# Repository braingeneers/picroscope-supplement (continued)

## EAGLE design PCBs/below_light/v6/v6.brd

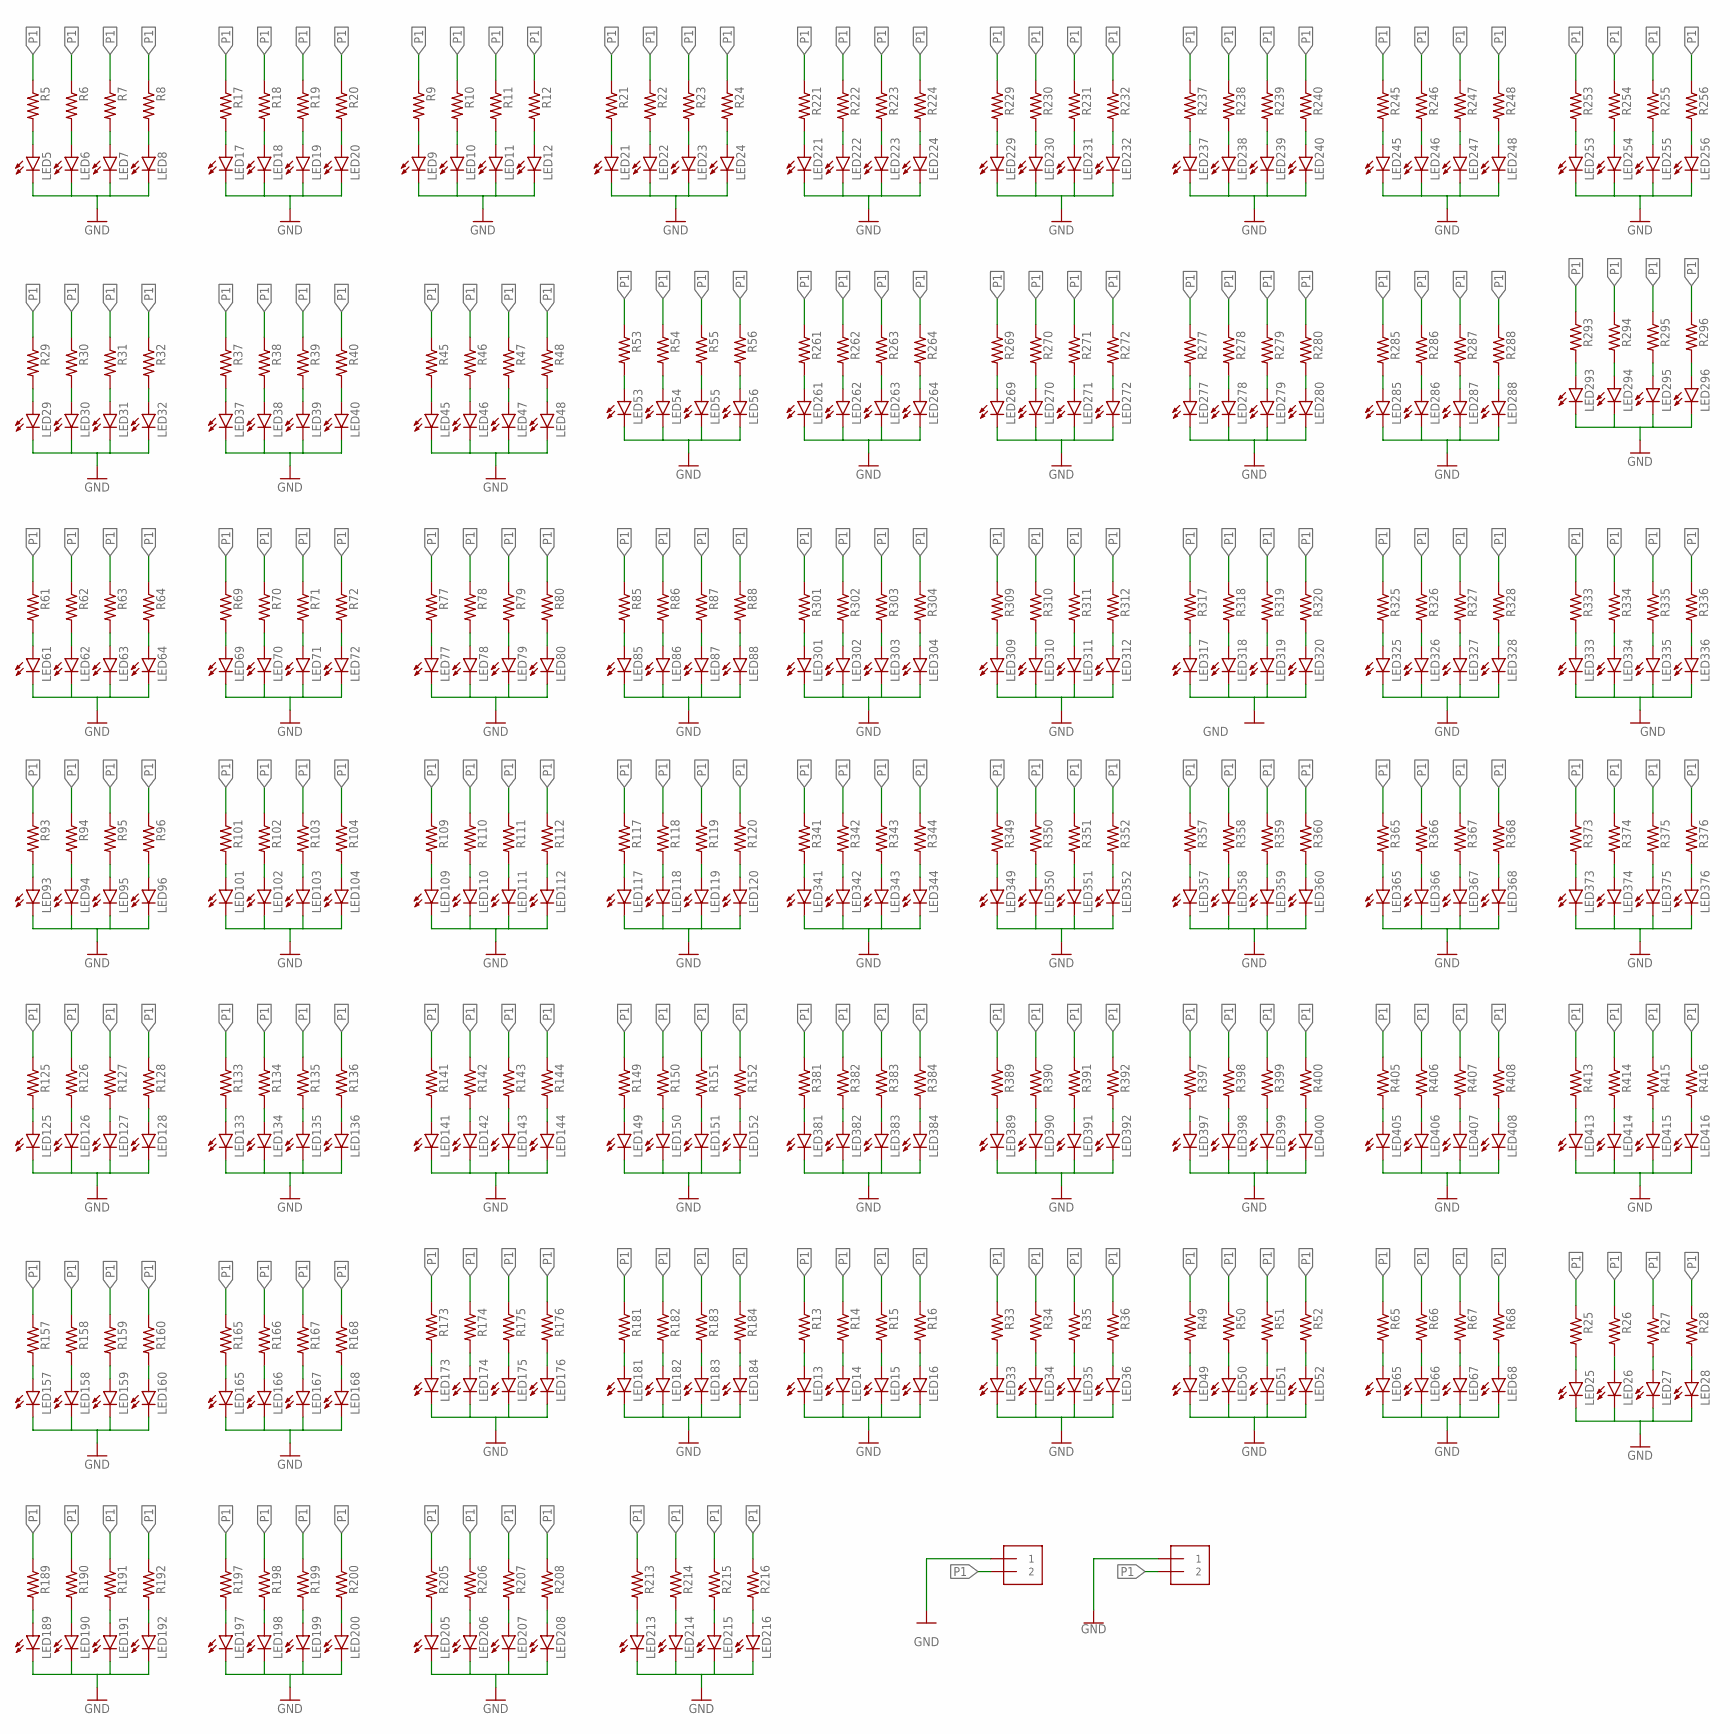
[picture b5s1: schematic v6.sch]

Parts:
LED5, LED6, LED7, LED8, LED9, LED10, LED11, LED12, LED13, LED14, LED15, LED16, LED17, LED18, LED19, LED20, LED21, LED22, LED23, LED24, LED25, LED26, LED27, LED28, LED29, LED30, LED31, LED32, LED33, LED34, LED35, LED36, LED37, LED38, LED39, LED40, LED45, LED46, LED47, LED48, LED49, LED50, LED51, LED52, LED53, LED54, LED55, LED56, LED61, LED62, LED63, LED64, LED65, LED66, LED67, LED68, LED69, LED70, LED71, LED72, LED77, LED78, LED79, LED80, LED85, LED86, LED87, LED88, LED93, LED94, LED95, LED96, LED101, LED102, LED103, LED104, LED109, LED110, LED111, LED112, LED117, LED118, LED119, LED120, LED125, LED126, LED127, LED128, LED133, LED134, LED135, LED136, LED141, LED142, LED143, LED144, LED149, LED150, LED151, LED152, LED157, LED158, LED159, LED160, LED165, LED166, LED167, LED168, LED173, LED174, LED175, LED176, LED181, LED182, LED183, LED184, LED189, LED190, LED191, LED192, LED197, LED198, LED199, LED200, LED205, LED206, LED207, LED208, LED213, LED214, LED215, LED216, LED221, LED222, LED223, LED224, LED229, LED230, LED231, LED232, LED237, LED238, LED239, LED240, LED245, LED246, LED247, LED248, LED253, LED254, LED255, LED256, LED261, LED262, LED263, LED264, LED269, LED270, LED271, LED272, LED277, LED278, LED279, LED280, LED285, LED286, LED287, LED288, LED293, LED294, LED295, LED296, LED301, LED302, LED303, LED304, LED309, LED310, LED311, LED312, LED317, LED318, LED319, LED320, LED325, LED326, LED327, LED328, LED333, LED334, LED335, LED336, LED341, LED342, LED343, LED344, LED349, LED350, LED351, LED352, LED357, LED358, LED359, LED360, LED365, LED366, LED367, LED368, LED373, LED374, LED375, LED376, LED381, LED382, LED383, LED384, LED389, LED390, LED391, LED392, LED397, LED398, LED399, LED400, LED405, LED406, LED407, LED408, LED413, LED414, LED415, LED416: LEDCHIP-LED0603; CHIP-LED0603
R5, R6, R7, R8, R9, R10, R11, R12, R13, R14, R15, R16, R17, R18, R19, R20, R21, R22, R23, R24, R25, R26, R27, R28, R29, R30, R31, R32, R33, R34, R35, R36, R37, R38, R39, R40, R45, R46, R47, R48, R49, R50, R51, R52, R53, R54, R55, R56, R61, R62, R63, R64, R65, R66, R67, R68, R69, R70, R71, R72, R77, R78, R79, R80, R85, R86, R87, R88, R93, R94, R95, R96, R101, R102, R103, R104, R109, R110, R111, R112, R117, R118, R119, R120, R125, R126, R127, R128, R133, R134, R135, R136, R141, R142, R143, R144, R149, R150, R151, R152, R157, R158, R159, R160, R165, R166, R167, R168, R173, R174, R175, R176, R181, R182, R183, R184, R189, R190, R191, R192, R197, R198, R199, R200, R205, R206, R207, R208, R213, R214, R215, R216, R221, R222, R223, R224, R229, R230, R231, R232, R237, R238, R239, R240, R245, R246, R247, R248, R253, R254, R255, R256, R261, R262, R263, R264, R269, R270, R271, R272, R277, R278, R279, R280, R285, R286, R287, R288, R293, R294, R295, R296, R301, R302, R303, R304, R309, R310, R311, R312, R317, R318, R319, R320, R325, R326, R327, R328, R333, R334, R335, R336, R341, R342, R343, R344, R349, R350, R351, R352, R357, R358, R359, R360, R365, R366, R367, R368, R373, R374, R375, R376, R381, R382, R383, R384, R389, R390, R391, R392, R397, R398, R399, R400, R405, R406, R407, R408, R413, R414, R415, R416: R-US_R0603; R0603
U$1, U$2: MOLEX_0039301022; MINI-FIT_JR_CONN

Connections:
GNDSSS: LED5.C, LED6.C, LED7.C, LED8.C, LED9.C, LED10.C, LED11.C, LED12.C, LED13.C, LED14.C, LED15.C, LED16.C, LED17.C, LED18.C, LED19.C, LED20.C, LED21.C, LED22.C, LED23.C, LED24.C, LED25.C, LED26.C, LED27.C, LED28.C, LED29.C, LED30.C, LED31.C, LED32.C, LED33.C, LED34.C, LED35.C, LED36.C, LED37.C, LED38.C, LED39.C, LED40.C, LED45.C, LED46.C, LED47.C, LED48.C, LED49.C, LED50.C, LED51.C, LED52.C, LED53.C, LED54.C, LED55.C, LED56.C, LED61.C, LED62.C, LED63.C, LED64.C, LED65.C, LED66.C, LED67.C, LED68.C, LED69.C, LED70.C, LED71.C, LED72.C, LED77.C, LED78.C, LED79.C, LED80.C, LED85.C, LED86.C, LED87.C, LED88.C, LED93.C, LED94.C, LED95.C, LED96.C, LED101.C, LED102.C, LED103.C, LED104.C, LED109.C, LED110.C, LED111.C, LED112.C, LED117.C, LED118.C, LED119.C, LED120.C, LED125.C, LED126.C, LED127.C, LED128.C, LED133.C, LED134.C, LED135.C, LED136.C, LED141.C, LED142.C, LED143.C, LED144.C, LED149.C, LED150.C, LED151.C, LED152.C, LED157.C, LED158.C, LED159.C, LED160.C, LED165.C, LED166.C, LED167.C, LED168.C, LED173.C, LED174.C, LED175.C, LED176.C, LED181.C, LED182.C, LED183.C, LED184.C, LED189.C, LED190.C, LED191.C, LED192.C, LED197.C, LED198.C, LED199.C, LED200.C, LED205.C, LED206.C, LED207.C, LED208.C, LED213.C, LED214.C, LED215.C, LED216.C, LED221.C, LED222.C, LED223.C, LED224.C, LED229.C, LED230.C, LED231.C, LED232.C, LED237.C, LED238.C, LED239.C, LED240.C, LED245.C, LED246.C, LED247.C, LED248.C, LED253.C, LED254.C, LED255.C, LED256.C, LED261.C, LED262.C, LED263.C, LED264.C, LED269.C, LED270.C, LED271.C, LED272.C, LED277.C, LED278.C, LED279.C, LED280.C, LED285.C, LED286.C, LED287.C, LED288.C, LED293.C, LED294.C, LED295.C, LED296.C, LED301.C, LED302.C, LED303.C, LED304.C, LED309.C, LED310.C, LED311.C, LED312.C, LED317.C, LED318.C, LED319.C, LED320.C, LED325.C, LED326.C, LED327.C, LED328.C, LED333.C, LED334.C, LED335.C, LED336.C, LED341.C, LED342.C, LED343.C, LED344.C, LED349.C, LED350.C, LED351.C, LED352.C, LED357.C, LED358.C, LED359.C, LED360.C, LED365.C, LED366.C, LED367.C, LED368.C, LED373.C, LED374.C, LED375.C, LED376.C, LED381.C, LED382.C, LED383.C, LED384.C, LED389.C, LED390.C, LED391.C, LED392.C, LED397.C, LED398.C, LED399.C, LED400.C, LED405.C, LED406.C, LED407.C, LED408.C, LED413.C, LED414.C, LED415.C, LED416.C, U$1.P$2 (1), U$2.P$2 (1)
unnamed: LED5.A, R5.2
unnamed: LED6.A, R6.2
unnamed: LED7.A, R7.2
unnamed: LED8.A, R8.2
unnamed: LED9.A, R9.2
unnamed: LED10.A, R10.2
unnamed: LED11.A, R11.2
unnamed: LED12.A, R12.2
unnamed: LED13.A, R13.2
unnamed: LED14.A, R14.2
unnamed: LED15.A, R15.2
unnamed: LED16.A, R16.2
unnamed: LED17.A, R17.2
unnamed: LED18.A, R18.2
unnamed: LED19.A, R19.2
unnamed: LED20.A, R20.2
unnamed: LED21.A, R21.2
unnamed: LED22.A, R22.2
unnamed: LED23.A, R23.2
unnamed: LED24.A, R24.2
unnamed: LED25.A, R25.2
unnamed: LED26.A, R26.2
unnamed: LED27.A, R27.2
unnamed: LED28.A, R28.2
unnamed: LED29.A, R29.2
unnamed: LED30.A, R30.2
unnamed: LED31.A, R31.2
unnamed: LED32.A, R32.2
unnamed: LED33.A, R33.2
unnamed: LED34.A, R34.2
unnamed: LED35.A, R35.2
unnamed: LED36.A, R36.2
unnamed: LED37.A, R37.2
unnamed: LED38.A, R38.2
unnamed: LED39.A, R39.2
unnamed: LED40.A, R40.2
unnamed: LED45.A, R45.2
unnamed: LED46.A, R46.2
unnamed: LED47.A, R47.2
unnamed: LED48.A, R48.2
unnamed: LED49.A, R49.2
unnamed: LED50.A, R50.2
unnamed: LED51.A, R51.2
unnamed: LED52.A, R52.2
unnamed: LED53.A, R53.2
unnamed: LED54.A, R54.2
unnamed: LED55.A, R55.2
unnamed: LED56.A, R56.2
unnamed: LED61.A, R61.2
unnamed: LED62.A, R62.2
unnamed: LED63.A, R63.2
unnamed: LED64.A, R64.2
unnamed: LED65.A, R65.2
unnamed: LED66.A, R66.2
unnamed: LED67.A, R67.2
unnamed: LED68.A, R68.2
unnamed: LED69.A, R69.2
unnamed: LED70.A, R70.2
unnamed: LED71.A, R71.2
unnamed: LED72.A, R72.2
unnamed: LED77.A, R77.2
unnamed: LED78.A, R78.2
unnamed: LED79.A, R79.2
unnamed: LED80.A, R80.2
unnamed: LED85.A, R85.2
unnamed: LED86.A, R86.2
unnamed: LED87.A, R87.2
unnamed: LED88.A, R88.2
unnamed: LED93.A, R93.2
unnamed: LED94.A, R94.2
unnamed: LED95.A, R95.2
unnamed: LED96.A, R96.2
unnamed: LED101.A, R101.2
unnamed: LED102.A, R102.2
unnamed: LED103.A, R103.2
unnamed: LED104.A, R104.2
unnamed: LED109.A, R109.2
unnamed: LED110.A, R110.2
unnamed: LED111.A, R111.2
unnamed: LED112.A, R112.2
unnamed: LED117.A, R117.2
unnamed: LED118.A, R118.2
unnamed: LED119.A, R119.2
unnamed: LED120.A, R120.2
unnamed: LED125.A, R125.2
unnamed: LED126.A, R126.2
unnamed: LED127.A, R127.2
unnamed: LED128.A, R128.2
unnamed: LED133.A, R133.2
unnamed: LED134.A, R134.2
unnamed: LED135.A, R135.2
unnamed: LED136.A, R136.2
unnamed: LED141.A, R141.2
unnamed: LED142.A, R142.2
unnamed: LED143.A, R143.2
unnamed: LED144.A, R144.2
unnamed: LED149.A, R149.2
unnamed: LED150.A, R150.2
unnamed: LED151.A, R151.2
unnamed: LED152.A, R152.2
unnamed: LED157.A, R157.2
unnamed: LED158.A, R158.2
unnamed: LED159.A, R159.2
unnamed: LED160.A, R160.2
unnamed: LED165.A, R165.2
unnamed: LED166.A, R166.2
unnamed: LED167.A, R167.2
unnamed: LED168.A, R168.2
unnamed: LED173.A, R173.2
unnamed: LED174.A, R174.2
unnamed: LED175.A, R175.2
unnamed: LED176.A, R176.2
unnamed: LED181.A, R181.2
unnamed: LED182.A, R182.2
unnamed: LED183.A, R183.2
unnamed: LED184.A, R184.2
unnamed: LED189.A, R189.2
unnamed: LED190.A, R190.2
unnamed: LED191.A, R191.2
unnamed: LED192.A, R192.2
unnamed: LED197.A, R197.2
unnamed: LED198.A, R198.2
unnamed: LED199.A, R199.2
unnamed: LED200.A, R200.2
unnamed: LED205.A, R205.2
unnamed: LED206.A, R206.2
unnamed: LED207.A, R207.2
unnamed: LED208.A, R208.2
unnamed: LED213.A, R213.2
unnamed: LED214.A, R214.2
unnamed: LED215.A, R215.2
unnamed: LED216.A, R216.2
unnamed: LED221.A, R221.2
unnamed: LED222.A, R222.2
unnamed: LED223.A, R223.2
unnamed: LED224.A, R224.2
unnamed: LED229.A, R229.2
unnamed: LED230.A, R230.2
unnamed: LED231.A, R231.2
unnamed: LED232.A, R232.2
unnamed: LED237.A, R237.2
unnamed: LED238.A, R238.2
unnamed: LED239.A, R239.2
unnamed: LED240.A, R240.2
unnamed: LED245.A, R245.2
unnamed: LED246.A, R246.2
unnamed: LED247.A, R247.2
unnamed: LED248.A, R248.2
unnamed: LED253.A, R253.2
unnamed: LED254.A, R254.2
unnamed: LED255.A, R255.2
unnamed: LED256.A, R256.2
unnamed: LED261.A, R261.2
unnamed: LED262.A, R262.2
unnamed: LED263.A, R263.2
unnamed: LED264.A, R264.2
unnamed: LED269.A, R269.2
unnamed: LED270.A, R270.2
unnamed: LED271.A, R271.2
unnamed: LED272.A, R272.2
unnamed: LED277.A, R277.2
unnamed: LED278.A, R278.2
unnamed: LED279.A, R279.2
unnamed: LED280.A, R280.2
unnamed: LED285.A, R285.2
unnamed: LED286.A, R286.2
unnamed: LED287.A, R287.2
unnamed: LED288.A, R288.2
unnamed: LED293.A, R293.2
unnamed: LED294.A, R294.2
unnamed: LED295.A, R295.2
unnamed: LED296.A, R296.2
unnamed: LED301.A, R301.2
unnamed: LED302.A, R302.2
unnamed: LED303.A, R303.2
unnamed: LED304.A, R304.2
unnamed: LED309.A, R309.2
unnamed: LED310.A, R310.2
unnamed: LED311.A, R311.2
unnamed: LED312.A, R312.2
unnamed: LED317.A, R317.2
unnamed: LED318.A, R318.2
unnamed: LED319.A, R319.2
unnamed: LED320.A, R320.2
unnamed: LED325.A, R325.2
unnamed: LED326.A, R326.2
unnamed: LED327.A, R327.2
unnamed: LED328.A, R328.2
unnamed: LED333.A, R333.2
unnamed: LED334.A, R334.2
unnamed: LED335.A, R335.2
unnamed: LED336.A, R336.2
unnamed: LED341.A, R341.2
unnamed: LED342.A, R342.2
unnamed: LED343.A, R343.2
unnamed: LED344.A, R344.2
unnamed: LED349.A, R349.2
unnamed: LED350.A, R350.2
unnamed: LED351.A, R351.2
unnamed: LED352.A, R352.2
unnamed: LED357.A, R357.2
unnamed: LED358.A, R358.2
unnamed: LED359.A, R359.2
unnamed: LED360.A, R360.2
unnamed: LED365.A, R365.2
unnamed: LED366.A, R366.2
unnamed: LED367.A, R367.2
unnamed: LED368.A, R368.2
unnamed: LED373.A, R373.2
unnamed: LED374.A, R374.2
unnamed: LED375.A, R375.2
unnamed: LED376.A, R376.2
unnamed: LED381.A, R381.2
unnamed: LED382.A, R382.2
unnamed: LED383.A, R383.2
unnamed: LED384.A, R384.2
unnamed: LED389.A, R389.2
unnamed: LED390.A, R390.2
unnamed: LED391.A, R391.2
unnamed: LED392.A, R392.2
unnamed: LED397.A, R397.2
unnamed: LED398.A, R398.2
unnamed: LED399.A, R399.2
unnamed: LED400.A, R400.2
unnamed: LED405.A, R405.2
unnamed: LED406.A, R406.2
unnamed: LED407.A, R407.2
unnamed: LED408.A, R408.2
unnamed: LED413.A, R413.2
unnamed: LED414.A, R414.2
unnamed: LED415.A, R415.2
unnamed: LED416.A, R416.2
P1: R5.1, R6.1, R7.1, R8.1, R9.1, R10.1, R11.1, R12.1, R13.1, R14.1, R15.1, R16.1, R17.1, R18.1, R19.1, R20.1, R21.1, R22.1, R23.1, R24.1, R25.1, R26.1, R27.1, R28.1, R29.1, R30.1, R31.1, R32.1, R33.1, R34.1, R35.1, R36.1, R37.1, R38.1, R39.1, R40.1, R45.1, R46.1, R47.1, R48.1, R49.1, R50.1, R51.1, R52.1, R53.1, R54.1, R55.1, R56.1, R61.1, R62.1, R63.1, R64.1, R65.1, R66.1, R67.1, R68.1, R69.1, R70.1, R71.1, R72.1, R77.1, R78.1, R79.1, R80.1, R85.1, R86.1, R87.1, R88.1, R93.1, R94.1, R95.1, R96.1, R101.1, R102.1, R103.1, R104.1, R109.1, R110.1, R111.1, R112.1, R117.1, R118.1, R119.1, R120.1, R125.1, R126.1, R127.1, R128.1, R133.1, R134.1, R135.1, R136.1, R141.1, R142.1, R143.1, R144.1, R149.1, R150.1, R151.1, R152.1, R157.1, R158.1, R159.1, R160.1, R165.1, R166.1, R167.1, R168.1, R173.1, R174.1, R175.1, R176.1, R181.1, R182.1, R183.1, R184.1, R189.1, R190.1, R191.1, R192.1, R197.1, R198.1, R199.1, R200.1, R205.1, R206.1, R207.1, R208.1, R213.1, R214.1, R215.1, R216.1, R221.1, R222.1, R223.1, R224.1, R229.1, R230.1, R231.1, R232.1, R237.1, R238.1, R239.1, R240.1, R245.1, R246.1, R247.1, R248.1, R253.1, R254.1, R255.1, R256.1, R261.1, R262.1, R263.1, R264.1, R269.1, R270.1, R271.1, R272.1, R277.1, R278.1, R279.1, R280.1, R285.1, R286.1, R287.1, R288.1, R293.1, R294.1, R295.1, R296.1, R301.1, R302.1, R303.1, R304.1, R309.1, R310.1, R311.1, R312.1, R317.1, R318.1, R319.1, R320.1, R325.1, R326.1, R327.1, R328.1, R333.1, R334.1, R335.1, R336.1, R341.1, R342.1, R343.1, R344.1, R349.1, R350.1, R351.1, R352.1, R357.1, R358.1, R359.1, R360.1, R365.1, R366.1, R367.1, R368.1, R373.1, R374.1, R375.1, R376.1, R381.1, R382.1, R383.1, R384.1, R389.1, R390.1, R391.1, R392.1, R397.1, R398.1, R399.1, R400.1, R405.1, R406.1, R407.1, R408.1, R413.1, R414.1, R415.1, R416.1, U$1.P$1 (2), U$2.P$1 (2)

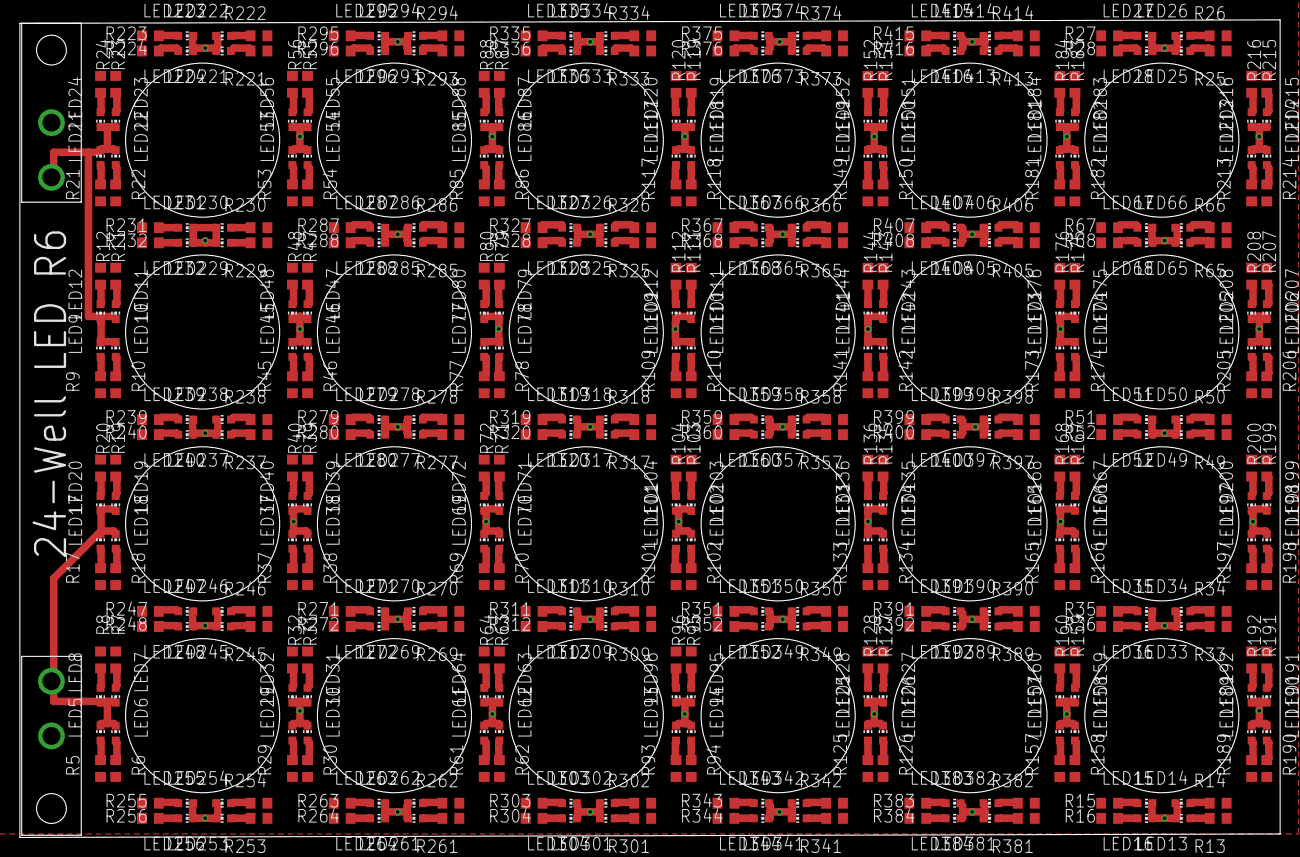
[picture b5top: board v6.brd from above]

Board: 2 copper layers, 126.8 x 82.2 mm, 466 parts (0 on the bottom side), 234 nets.

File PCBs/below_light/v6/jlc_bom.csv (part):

Comment,Designator,Footprint,LCSC Part #（optional）
LED,LED5,CHIP-LED0603,C389521
LED,LED6,CHIP-LED0603,C389521
LED,LED7,CHIP-LED0603,C389521
LED,LED8,CHIP-LED0603,C389521
LED,LED9,CHIP-LED0603,C389521
LED,LED10,CHIP-LED0603,C389521
LED,LED11,CHIP-LED0603,C389521
LED,LED12,CHIP-LED0603,C389521
LED,LED13,CHIP-LED0603,C389521
LED,LED14,CHIP-LED0603,C389521
LED,LED15,CHIP-LED0603,C389521
LED,LED16,CHIP-LED0603,C389521
LED,LED17,CHIP-LED0603,C389521
LED,LED18,CHIP-LED0603,C389521
LED,LED19,CHIP-LED0603,C389521
LED,LED20,CHIP-LED0603,C389521
LED,LED21,CHIP-LED0603,C389521
LED,LED22,CHIP-LED0603,C389521
LED,LED23,CHIP-LED0603,C389521
LED,LED24,CHIP-LED0603,C389521
LED,LED25,CHIP-LED0603,C389521
LED,LED26,CHIP-LED0603,C389521
LED,LED27,CHIP-LED0603,C389521
LED,LED28,CHIP-LED0603,C389521
LED,LED29,CHIP-LED0603,C389521
LED,LED30,CHIP-LED0603,C389521
LED,LED31,CHIP-LED0603,C389521
LED,LED32,CHIP-LED0603,C389521
LED,LED33,CHIP-LED0603,C389521
LED,LED34,CHIP-LED0603,C389521
LED,LED35,CHIP-LED0603,C389521
LED,LED36,CHIP-LED0603,C389521
LED,LED37,CHIP-LED0603,C389521
LED,LED38,CHIP-LED0603,C389521
LED,LED39,CHIP-LED0603,C389521
LED,LED40,CHIP-LED0603,C389521
LED,LED45,CHIP-LED0603,C389521
LED,LED46,CHIP-LED0603,C389521
LED,LED47,CHIP-LED0603,C389521
LED,LED48,CHIP-LED0603,C389521
LED,LED49,CHIP-LED0603,C389521
LED,LED50,CHIP-LED0603,C389521
LED,LED51,CHIP-LED0603,C389521
LED,LED52,CHIP-LED0603,C389521
LED,LED53,CHIP-LED0603,C389521
LED,LED54,CHIP-LED0603,C389521
LED,LED55,CHIP-LED0603,C389521
LED,LED56,CHIP-LED0603,C389521
LED,LED61,CHIP-LED0603,C389521
LED,LED62,CHIP-LED0603,C389521
LED,LED63,CHIP-LED0603,C389521
LED,LED64,CHIP-LED0603,C389521
LED,LED65,CHIP-LED0603,C389521
LED,LED66,CHIP-LED0603,C389521
LED,LED67,CHIP-LED0603,C389521
LED,LED68,CHIP-LED0603,C389521
LED,LED69,CHIP-LED0603,C389521
LED,LED70,CHIP-LED0603,C389521
LED,LED71,CHIP-LED0603,C389521
LED,LED72,CHIP-LED0603,C389521
LED,LED77,CHIP-LED0603,C389521
LED,LED78,CHIP-LED0603,C389521
LED,LED79,CHIP-LED0603,C389521
LED,LED80,CHIP-LED0603,C389521
LED,LED85,CHIP-LED0603,C389521
LED,LED86,CHIP-LED0603,C389521
LED,LED87,CHIP-LED0603,C389521
LED,LED88,CHIP-LED0603,C389521
LED,LED93,CHIP-LED0603,C389521
LED,LED94,CHIP-LED0603,C389521
LED,LED95,CHIP-LED0603,C389521
LED,LED96,CHIP-LED0603,C389521
LED,LED101,CHIP-LED0603,C389521
LED,LED102,CHIP-LED0603,C389521
LED,LED103,CHIP-LED0603,C389521
LED,LED104,CHIP-LED0603,C389521
LED,LED109,CHIP-LED0603,C389521
LED,LED110,CHIP-LED0603,C389521
LED,LED111,CHIP-LED0603,C389521
LED,LED112,CHIP-LED0603,C389521
LED,LED117,CHIP-LED0603,C389521
LED,LED118,CHIP-LED0603,C389521
LED,LED119,CHIP-LED0603,C389521
LED,LED120,CHIP-LED0603,C389521
LED,LED125,CHIP-LED0603,C389521
LED,LED126,CHIP-LED0603,C389521
LED,LED127,CHIP-LED0603,C389521
LED,LED128,CHIP-LED0603,C389521
LED,LED133,CHIP-LED0603,C389521
LED,LED134,CHIP-LED0603,C389521
LED,LED135,CHIP-LED0603,C389521
LED,LED136,CHIP-LED0603,C389521
LED,LED141,CHIP-LED0603,C389521
LED,LED142,CHIP-LED0603,C389521
LED,LED143,CHIP-LED0603,C389521
LED,LED144,CHIP-LED0603,C389521
LED,LED149,CHIP-LED0603,C389521
LED,LED150,CHIP-LED0603,C389521
LED,LED151,CHIP-LED0603,C389521
LED,LED152,CHIP-LED0603,C389521
LED,LED157,CHIP-LED0603,C389521
LED,LED158,CHIP-LED0603,C389521
LED,LED159,CHIP-LED0603,C389521
LED,LED160,CHIP-LED0603,C389521
LED,LED165,CHIP-LED0603,C389521
LED,LED166,CHIP-LED0603,C389521
LED,LED167,CHIP-LED0603,C389521
LED,LED168,CHIP-LED0603,C389521
LED,LED173,CHIP-LED0603,C389521
LED,LED174,CHIP-LED0603,C389521
LED,LED175,CHIP-LED0603,C389521
LED,LED176,CHIP-LED0603,C389521
LED,LED181,CHIP-LED0603,C389521
LED,LED182,CHIP-LED0603,C389521
LED,LED183,CHIP-LED0603,C389521
LED,LED184,CHIP-LED0603,C389521
LED,LED189,CHIP-LED0603,C389521
LED,LED190,CHIP-LED0603,C389521
LED,LED191,CHIP-LED0603,C389521
LED,LED192,CHIP-LED0603,C389521
LED,LED197,CHIP-LED0603,C389521
LED,LED198,CHIP-LED0603,C389521
LED,LED199,CHIP-LED0603,C389521
LED,LED200,CHIP-LED0603,C389521
LED,LED205,CHIP-LED0603,C389521
LED,LED206,CHIP-LED0603,C389521
LED,LED207,CHIP-LED0603,C389521
LED,LED208,CHIP-LED0603,C389521
LED,LED213,CHIP-LED0603,C389521
LED,LED214,CHIP-LED0603,C389521
LED,LED215,CHIP-LED0603,C389521
LED,LED216,CHIP-LED0603,C389521
LED,LED221,CHIP-LED0603,C389521
LED,LED222,CHIP-LED0603,C389521
LED,LED223,CHIP-LED0603,C389521
LED,LED224,CHIP-LED0603,C389521
LED,LED229,CHIP-LED0603,C389521
LED,LED230,CHIP-LED0603,C389521
LED,LED231,CHIP-LED0603,C389521
LED,LED232,CHIP-LED0603,C389521
LED,LED237,CHIP-LED0603,C389521
LED,LED238,CHIP-LED0603,C389521
LED,LED239,CHIP-LED0603,C389521
LED,LED240,CHIP-LED0603,C389521
LED,LED245,CHIP-LED0603,C389521
LED,LED246,CHIP-LED0603,C389521
LED,LED247,CHIP-LED0603,C389521
LED,LED248,CHIP-LED0603,C389521
LED,LED253,CHIP-LED0603,C389521
LED,LED254,CHIP-LED0603,C389521
LED,LED255,CHIP-LED0603,C389521
LED,LED256,CHIP-LED0603,C389521
LED,LED261,CHIP-LED0603,C389521
LED,LED262,CHIP-LED0603,C389521
LED,LED263,CHIP-LED0603,C389521
LED,LED264,CHIP-LED0603,C389521
LED,LED269,CHIP-LED0603,C389521
LED,LED270,CHIP-LED0603,C389521
LED,LED271,CHIP-LED0603,C389521
LED,LED272,CHIP-LED0603,C389521
LED,LED277,CHIP-LED0603,C389521
LED,LED278,CHIP-LED0603,C389521
LED,LED279,CHIP-LED0603,C389521
LED,LED280,CHIP-LED0603,C389521
LED,LED285,CHIP-LED0603,C389521
LED,LED286,CHIP-LED0603,C389521
LED,LED287,CHIP-LED0603,C389521
LED,LED288,CHIP-LED0603,C389521
LED,LED293,CHIP-LED0603,C389521
LED,LED294,CHIP-LED0603,C389521
LED,LED295,CHIP-LED0603,C389521
LED,LED296,CHIP-LED0603,C389521
LED,LED301,CHIP-LED0603,C389521
LED,LED302,CHIP-LED0603,C389521
LED,LED303,CHIP-LED0603,C389521
LED,LED304,CHIP-LED0603,C389521
LED,LED309,CHIP-LED0603,C389521
LED,LED310,CHIP-LED0603,C389521
LED,LED311,CHIP-LED0603,C389521
LED,LED312,CHIP-LED0603,C389521
LED,LED317,CHIP-LED0603,C389521
LED,LED318,CHIP-LED0603,C389521
LED,LED319,CHIP-LED0603,C389521
LED,LED320,CHIP-LED0603,C389521
LED,LED325,CHIP-LED0603,C389521
LED,LED326,CHIP-LED0603,C389521
LED,LED327,CHIP-LED0603,C389521
LED,LED328,CHIP-LED0603,C389521
LED,LED333,CHIP-LED0603,C389521
LED,LED334,CHIP-LED0603,C389521
LED,LED335,CHIP-LED0603,C389521
LED,LED336,CHIP-LED0603,C389521
LED,LED341,CHIP-LED0603,C389521
LED,LED342,CHIP-LED0603,C389521
LED,LED343,CHIP-LED0603,C389521
LED,LED344,CHIP-LED0603,C389521
LED,LED349,CHIP-LED0603,C389521
LED,LED350,CHIP-LED0603,C389521
LED,LED351,CHIP-LED0603,C389521
LED,LED352,CHIP-LED0603,C389521
LED,LED357,CHIP-LED0603,C389521
LED,LED358,CHIP-LED0603,C389521
LED,LED359,CHIP-LED0603,C389521
LED,LED360,CHIP-LED0603,C389521
LED,LED365,CHIP-LED0603,C389521
LED,LED366,CHIP-LED0603,C389521
LED,LED367,CHIP-LED0603,C389521
LED,LED368,CHIP-LED0603,C389521
LED,LED373,CHIP-LED0603,C389521
LED,LED374,CHIP-LED0603,C389521
LED,LED375,CHIP-LED0603,C389521
LED,LED376,CHIP-LED0603,C389521
LED,LED381,CHIP-LED0603,C389521
LED,LED382,CHIP-LED0603,C389521
LED,LED383,CHIP-LED0603,C389521
LED,LED384,CHIP-LED0603,C389521
LED,LED389,CHIP-LED0603,C389521
LED,LED390,CHIP-LED0603,C389521
LED,LED391,CHIP-LED0603,C389521
LED,LED392,CHIP-LED0603,C389521
LED,LED397,CHIP-LED0603,C389521
LED,LED398,CHIP-LED0603,C389521
LED,LED399,CHIP-LED0603,C389521
LED,LED400,CHIP-LED0603,C389521
LED,LED405,CHIP-LED0603,C389521
LED,LED406,CHIP-LED0603,C389521
LED,LED407,CHIP-LED0603,C389521
LED,LED408,CHIP-LED0603,C389521
LED,LED413,CHIP-LED0603,C389521
LED,LED414,CHIP-LED0603,C389521
LED,LED415,CHIP-LED0603,C389521
LED,LED416,CHIP-LED0603,C389521
Resistor,R5,R0603,C22775
Resistor,R6,R0603,C22775
Resistor,R7,R0603,C22775
Resistor,R8,R0603,C22775
Resistor,R9,R0603,C22775
Resistor,R10,R0603,C22775
Resistor,R11,R0603,C22775
Resistor,R12,R0603,C22775
Resistor,R13,R0603,C22775
Resistor,R14,R0603,C22775
Resistor,R15,R0603,C22775
Resistor,R16,R0603,C22775
Resistor,R17,R0603,C22775
Resistor,R18,R0603,C22775
Resistor,R19,R0603,C22775
Resistor,R20,R0603,C22775
Resistor,R21,R0603,C22775
Resistor,R22,R0603,C22775
Resistor,R23,R0603,C22775
Resistor,R24,R0603,C22775
Resistor,R25,R0603,C22775
Resistor,R26,R0603,C22775
Resistor,R27,R0603,C22775
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
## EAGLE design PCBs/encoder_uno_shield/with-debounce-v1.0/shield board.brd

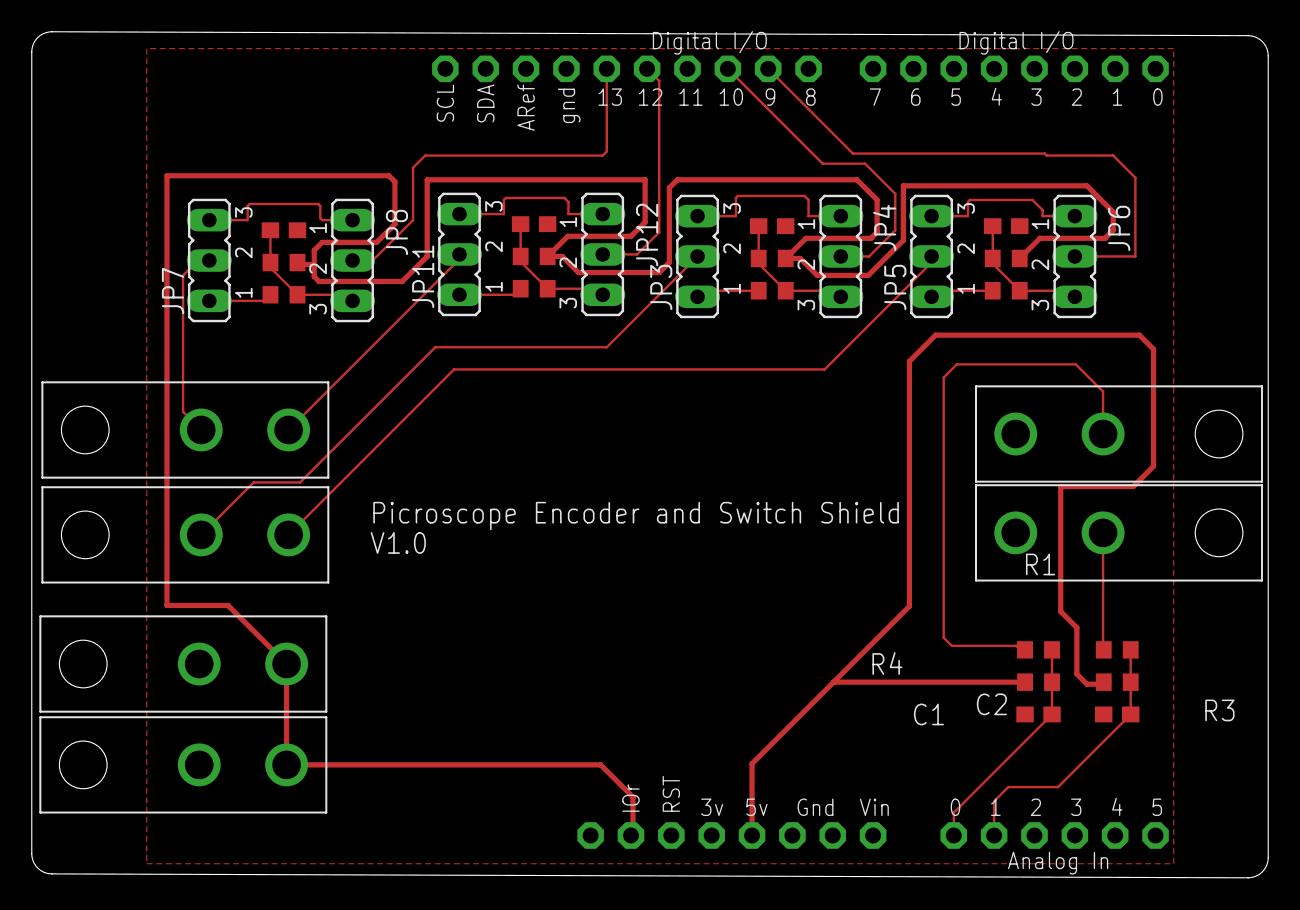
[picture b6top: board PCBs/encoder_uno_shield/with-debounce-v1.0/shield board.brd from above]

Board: 2 copper layers, 77.8 x 53.3 mm, 33 parts (0 on the bottom side), 26 nets.

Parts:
C1, C2, C4, C5, C6, C8: 0.1uF; C0603
JP3, JP4, JP5, JP6, JP7, JP8, JP11, JP12: JP2
R1, R3, R7, R9, R11, R15: 1k; R0603
R2, R4, R8, R10, R12, R16: 10k; R0603
U1: ARDUINOR3-BPLACE
U$1, U$2, U$3, U$4, U$5, U$6: MOLEX_0039301022; MINI-FIT_JR_CONN

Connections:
E1CHA: JP12.2, U1.D12
E1CHA_BYPASS: JP11.3, JP12.1
E1CHA_DB: C8.1, JP12.3, R15.2, R16.1
E1CHA_RAW: JP11.2, U$5.P$2
E1CHB: JP8.2, U1.D13
E1CHB_BYPASS: JP7.3, JP8.1
E1CHB_DB: C6.1, JP8.3, R11.2, R12.1
E1CHB_RAW: JP7.2, U$5.P$1
E2CHA: JP6.2, U1.D9
E2CHA_BYPASS: JP5.3, JP6.1
E2CHA_DB: C4.1, JP6.3, R7.2, R8.1
E2CHA_RAW: JP5.2, U$6.P$2
E2CHB: JP4.2, U1.D10
E2CHB_BYPASS: JP3.3, JP4.1
E2CHB_DB: C5.1, JP4.3, R9.2, R10.1
E2CHB_RAW: JP3.2, U$6.P$1
GND: C1.2, C2.2, C4.2, C5.2, C6.2, C8.2, U1.GND, U$1.P$2, U$2.P$2, U$3.P$1, U$4.P$1
unnamed: R1.1, U$1.P$1
unnamed: JP5.1, R7.1
unnamed: R3.1, U$2.P$1
unnamed: JP3.1, R9.1
unnamed: JP7.1, R11.1
unnamed: JP11.1, R15.1
SW_X: C1.1, R3.2, R4.1, U1.A0
SW_Y: C2.1, R1.2, R2.1, U1.A1
VCC: R2.2, R4.2, R8.2, R10.2, R12.2, R16.2, U1.5V, U1.IOREF, U$3.P$2, U$4.P$2

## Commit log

2021-11-16 init
2021-12-13 Picroscope CAD files
2022-03-15 added v1 of uno shield for connecting XY limit switches and motor encoders
2022-03-15 added .gitignore
2022-03-15 added debounce to sch, about to delete and add back as design block
2022-03-15 jumper togglable debounce circuit added for encoders
2022-03-17 moved components to bottom layer
2022-03-18 moved components and wires back to top layer
2022-03-18 made new version optimized for cnc routing
2022-03-25 realized i only need one switch port, about to redesign
2022-03-25 routed new board design
2022-04-15 fixed orientation of molex connectors in encoder shield
2022-04-16 moved molex connectors further out to the edge
2022-05-13 updated overheadlight eaglefile
2022-06-13 added encoder board
2022-08-22 Delete Limit switch stopper again v3.stl
    old peice
2022-08-23 CAD update Aug 22 2022
2022-08-23 CAD purge 1
2022-08-23 added new version of encoder board
